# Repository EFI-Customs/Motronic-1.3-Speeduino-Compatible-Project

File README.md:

# Speeduino Compatible BMW ECU's

This is the main repository containing base maps for various BMW engines utilising the Speeduino Compatible PCB's from EFI Customs.

As well as this, you will find documentation on building your own PCB's.

# Base Maps

It is important to note that these base maps are not intended to be a "ready to go" tune. 

These are purely used as a starting point to get your project going without having to go through the time-consuming process of tweaking every setting.

It is also important to verify your timing with a light before you crank your engine with injectors firing, otherwise you may cause some damage to your motor (not good!). 
These base maps have been preset to be 50deg ATDC (After Top Dead Centre, as opposed to the typical Before Top Dead Centre values used in other kinds of standalone ECU's), which seems to be a typical expected value on a stock M20 running factory single ignition coil. 

Lastly, these base maps have been built under the assumption that a MAX992x based VR Conditioner for the crank sensor. As such, the Trigger Edge is set to RISING. If you are running another type of VR Conditioner or you've converted to Hall Effect then please ensure you have checked this setting before cranking. Remember that if you have switched over to a Hall Effect crank sensor then you need to change jumper configuration on the PCB. There is a jumper configuration table located on the silkscreen underneath where the Arduino mounts.

You can also achieve your own base map by using the Speeduino base maps found here: [Official and user contributed base tunes for Speeduino installations](https://github.com/speeduino/Tunes)

## Motronic 1.3 General Information & Observations
These instructions are designed for the V1.7 Motronic 1.3 Board.
For the Motronic 1.3 compatible ECU, please ensure you have done;

### Air Flow Meter (AFM)
Assuming you are keeping your AFM, unplug the AFM connector and add wires to pins 1 & 4 on the plug and connect them to pins 1 & 4 on the AFM. 
Doing so allows us to utilise the factory intake air temperature sensor. 

The reason we need to unplug pins 2 & 3 is because they go to the External MAP and +5V line on the ECU pins 7 and 12 respectively. 
If you do not do this, you will find that your MAP reading will halve, and you will experience signal noise.

If you intend to delete the AFM, you can instead run any generic intake temperature sensor. A very popular one is an Open Element GM IAT sensor. Again, you can just wire this sensor into the factory AFM harness (pins 1 & 4).

### TPS
If you want to start the car without re-wiring the TPS, simply unplug it and manually enter values in the TPS calibration window to spoof readings. 
However, on a full implementation of this board it is highly recommended to convert to an M50 style TPS.

To convert your TPS to the M50 one you need to do the following:

 - Acquire M50 TPS (Part number 13 63 1 721 456)
 - Acquire M50 TPS Adapter 
 - Swap pins 1 (Brown/Blue) and 2 (Brown) on the factory TPS Connector

### Ignition

If you are running factory ignition and you have the cylinder 1 pulse sensor attached (image link here: https://www.r3vlimited.com/board/filedata/fetch?id=7225671) you need to unplug the sensor from the engine harness. 

The Motronic PCB's support individual coil-on-plug for up to 4 cyl engines (needs Cam Position Sensor retrofitted) and wasted-spark for 6-cyl engines. To retrofit a cam sensor you can re-use the cylinder 1 pulse sensor plug on the engine harness side. A MAX9926 VR Conditioner accepts two inputs (crank + cam).

The principle remains similar for both platforms, but we will cover the most common Wasted Spark conversion for an M20.

There are multiple approaches to converting to Wasted Spark, we'll cover the two easiest:

#### Method 1 - Retain the factory coil wiring (black wire and green wire)
The Motronic 1.3 PCB has an external ignition connector for additional channels, for this method you need to add two wires that go from the Ign 2.1 and 3.1 channels on the connector to the respective coils. 
In total, you will have three ignition channel wires and one +12V (green) wire.
The factory black wire will act as channel 1 ignition, 2.1 (PCB) is channel 2 and 3.1 (PCB) is channel 3.

#### Method 2 - Utilise the external connector exclusively
As the title suggests, we either remove or hide the factory black ignition wire and run the 3 channels exclusively from the external ignition connector on the ECU PCB.

Channel 1.1, 2.1 and 3.1 on the PCB are channels 1,2,3 respectively. 
With this method, we still retain the factory green coil wire to provide switched +12V.

#### Ignition wiring continued
We have used a GM V6 Coil Pack with a gutted and re-wired DFI module.

Reference Delphi Coil Pack Part Number: GN10123

Reference Delphi DFI Module Part Number: CM414

Reference DFI Module wiring guide: https://www.e30zone.net/e30wiki/images/9/9a/Gmgutted.jpg

Another wiring reference image: http://i.imgur.com/Q9WdHVS.png

Use a multimeter to ensure you have connected the respective wires to the appropriate pins on the DFI Module.
+12V should be a shared pin across all three pairs of pins (usually the left pin on each pair)
Then channels 1-3 will be individual pins (i.e. not shared).

Label your coil packs with the cylinders they will supply spark for.

- Channel 1 -> 1-6
- Channel 2 -> 2-5
- Channel 3 -> 3-4

Install the DFI module and run some new ignition leads to your spark plugs.
Connect the new wiring from the DFI module into your Motronic PCB External Ignition Connector.
#### TunerStudio settings
With wasted spark installed, you will need to change a few things in your tune file.

Firstly, you need to go into `"Settings" -> "Trigger Setup"` and change the `Trigger Angle` from `50` to `276`. The M20 has a trigger angle of 84 deg BTDC. 
360 - 84 = 276. **This trigger angle is a starting reference point and shouldn't be your final value until you have verified this with a timing light!!** 
Our 2.9 stroker M20 reads 88 deg BTDC which equates to 272 ATDC trigger angle.

Secondly, go to `"Spark" -> "Spark Settings"` and change `"Spark Output Mode"` to `"Wasted Spark"`.
That's it! Wasted Spark is now ready to go.

### Injection
The factory injector wiring is designed to run in a batched manner. Unfortunately, the Speeduino firmware does not support batched injection. To make this work our base maps use untimed or simultaneous injection. 
This isn't perfect and will likely run rich. Tuning this also becomes rather difficult. 
The best approach for this is to convert our injector wiring to a paired setup.

This process can be done in a way that makes it fully reversible. While it's not necessarily the perfect solution, it worked for us when we needed to revert the injector wiring to meet specific requirements.

Starting with a Series 1 E30 M20 injector harness (this can be done with a series 2 harness, but requires a bit more finesse), we separated all the wires. We routed the brown/yellow wires (cylinders 2, 4, 6) and the brown/white wires (cylinders 1, 3, 5) to a 6-pin Deutsch connector, labeling them 1 through 6 accordingly. A multimeter was used to verify the correct wiring for each injector.

We also separated the temperature sensor wires and connected them to a 4-pin Deutsch connector.

The engine harness requires two 4-pin Deutsch connectors—one for the temperature sensor wires, and another for Injector Channels 1, 2, and 3, along with the injector 12V+ (which typically comes into the from the main relay/DME relay).

Next, it's time to create an adapter. Take a 6-pin Deutsch connector and wire it to match the one on the injector harness. On the other end, merge the injector pairs: cylinders 1 & 6 to Channel 1, cylinders 2 & 5 to Channel 2, and cylinders 3 & 4 to Channel 3. Wire these into a 4-pin Deutsch connector that aligns with the engine harness plug. Lastly, combine all the injector 12V+ wires (these are Red/White) into a single thicker cable (we used 12AWG wire for this) and connect it to the final open port on the 4-pin Deutsch connector.

For the third injector channel, route the wire neatly into the factory harness and run it back to the ECU, where it connects to the 3rd Channel output (bottom left) on the External Injector Connector of the PCB.

This setup gives you a flexible injector harness that can be adjusted as needed. In our case, we created two adapters—one for paired injectors and one for batch firing.

### MAP/Vacuum
Run a vacuum hose from the intake manifold to where your ECU is installed. You can get a T-Piece adapter and run the vacuum hose from between the intake manifold and the fuel pressure regulator.

### Wideband
Install a wideband controller and gauge. One we have used many times before is the Innovate LC-2. This comes with the controller, sensor, gauge and supports two programmable sensor outputs.

Refer to the instruction manual for installation and wiring or inquire with your preferred auto electrician.

For our installation, we have grounded our sensors to the ECU (using the expansion pads located underneath the Arduino) and re-programmed the LC-2's second sensor output to Wideband and wired it to the middle-bottom pin of the black IO connector on the Motronic PCB.

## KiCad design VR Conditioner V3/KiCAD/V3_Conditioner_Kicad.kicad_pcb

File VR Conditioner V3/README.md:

This is a design based on the Speeduino V3 VR Conditioner that you can find [here](https://github.com/speeduino/Hardware/tree/main/VR%20Conditioner/Prior%20Versions/v3)

It is electronically identical but has been converted to a KiCAD project and uses smaller footprints for the additional resistors and a revised circuit board package size.

I have provided the KiCAD project files in the KiCAD directory. The Gerber, BOM and Positions files are available so that you may easily order from JLCPCB. Note that the jumper, 2 resistors and empty 8 pin DIP socket will come back as unpopulated when requesting PCB assembly.

This design is released under the [CERN Open Hardware License v2 Strong (CERN-OHL-S)](https://ohwr.org/cern_ohl_s_v2.txt) license. This license is similar to the GPL, however is designed specifically for hardware design files, including PCB layouts and schematics. As the 'strongly reciprocal' version of the CERN OHL is used, you may use, copy, modify and create variations of these designs freely, provided that any changes or variations are also released under this CERN-OHL-S.

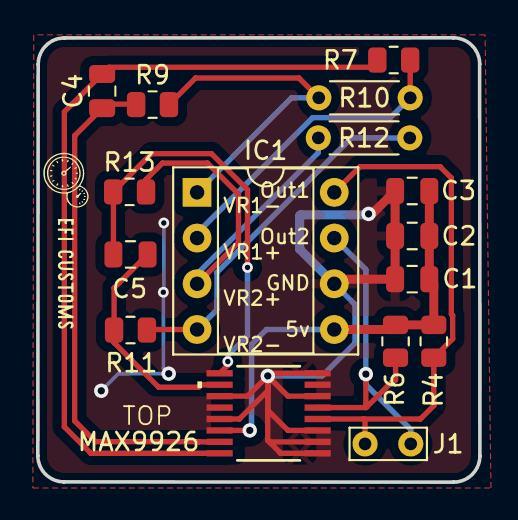
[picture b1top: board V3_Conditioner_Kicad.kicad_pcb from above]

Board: 2 copper layers, 24.6 x 24.7 mm, 16 parts (0 on the bottom side), 12 nets.

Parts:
C1: CC0805ZRY5V9BB104; C_0805_2012Metric
C2: CC0805KRX7R9BB103; C_0805_2012Metric
C3: CC0805KKX7R7BB105; C_0805_2012Metric
C4, C5: CC0805KRX7R9BB102; C_0805_2012Metric
IC1: DIP-8_W7.62mm_Socket
J1: Jumper_2_Open; TestPoint_Bridge_Pitch2.54mm_Drill0.7mm
MAX9926: MAX9926UAEE+T; 21-0055H_16_MXM
R4, R6: RC0805FR-071KL; R_0805_2012Metric
R7, R9, R11, R13: RC0805JR-0710KL; R_0805_2012Metric
R10, R12: 4.7k; R_Axial_DIN0204_L3.6mm_D1.6mm_P5.08mm_Horizontal

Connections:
+5V: C1.1, C2.1, C3.1, IC1.5 (+5V), MAX9926.14, R4.1, R6.1
GND: C1.2, C2.2, C3.2, IC1.6 (GND), MAX9926.1, MAX9926.2, MAX9926.3, MAX9926.6, MAX9926.8, MAX9926.11, MAX9926.13
unnamed: C4.1, MAX9926.16, R7.1
unnamed: C4.2, MAX9926.15, R9.1
unnamed: C5.1, MAX9926.10, R11.1
unnamed: C5.2, MAX9926.9, R13.1
Output1: IC1.8 (Output_1), J1.1 (A), MAX9926.4, R4.2
Output2: IC1.7 (Output_2), J1.1 (A), MAX9926.5, R6.2
VR1+: IC1.2 (VR1+), R7.2, R10.1
VR1-: IC1.1 (VR1-), R9.2, R10.2
VR2+: IC1.3 (VR2+), R12.2, R13.2
VR2-: IC1.4 (VR2-), R11.2, R12.1

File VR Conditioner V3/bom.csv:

Designator,Footprint,Quantity,Value,LCSC Part #
C1,0805,1,CC0805ZRY5V9BB104 ,
C2,0805,1,CC0805KRX7R9BB103 ,
C3,0805,1,CC0805KKX7R7BB105 ,
"C4, C5",0805,2,CC0805KRX7R9BB102,
MAX9926,21-0055H_16_MXM,1,MAX9926UAEE+T,
"R11, R13, R7, R9",0805,4,RC0805JR-0710KL ,
"R4, R6",0805,2,RC0805FR-071KL ,

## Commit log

2022-11-27 Adding M20 base maps
    Adding base maps that are identical in everything except for:
    -Engine Constants Required Fuel calculations
    -Fuel VE Maps
    Fuel VE Maps generated using the built in TunerStudio VE Table generator.
    Verified on stock M20B20 and modified M20B29
2022-11-27 Create README.md
    adding basic readme
2023-08-30 Add files via upload
    Uploading Motronic 1.3 User Guide v.1
2023-11-08 Adding v1 of assembly guide
2024-01-30 Updating User Guide
    Updating user guide steps outlining pinout for ECU connectors
2024-01-30 Adding Bill of materials file
    File contains individual component details
2024-09-09 Updating Assembly Guide
    Adding more verbose instructions about header pins on control boards
2024-09-24 Update README.md
    Making injector harness diagram correction + better worded explanation
2024-09-24 Update README.md
    Updating diagram with easier colours
2024-10-14 Create Jetronic To Motronic Conversion.md
    adding this document as a draft
2024-10-15 Update Jetronic To Motronic Conversion.md
    adding diagrams and improving main relay wiring description
2024-10-21 Update Jetronic To Motronic Conversion.md
    adding details regarding blue coolant sensor
2024-11-13 Update Jetronic To Motronic Conversion.md
    adding reference image for welding trigger wheel to crank pulley
2025-01-08 adding VR conditioner production files and original KiCAD project files

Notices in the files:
VR Conditioner V3/KiCAD/V3_Conditioner_Kicad.kicad_pcb:
© Josh Stewart
